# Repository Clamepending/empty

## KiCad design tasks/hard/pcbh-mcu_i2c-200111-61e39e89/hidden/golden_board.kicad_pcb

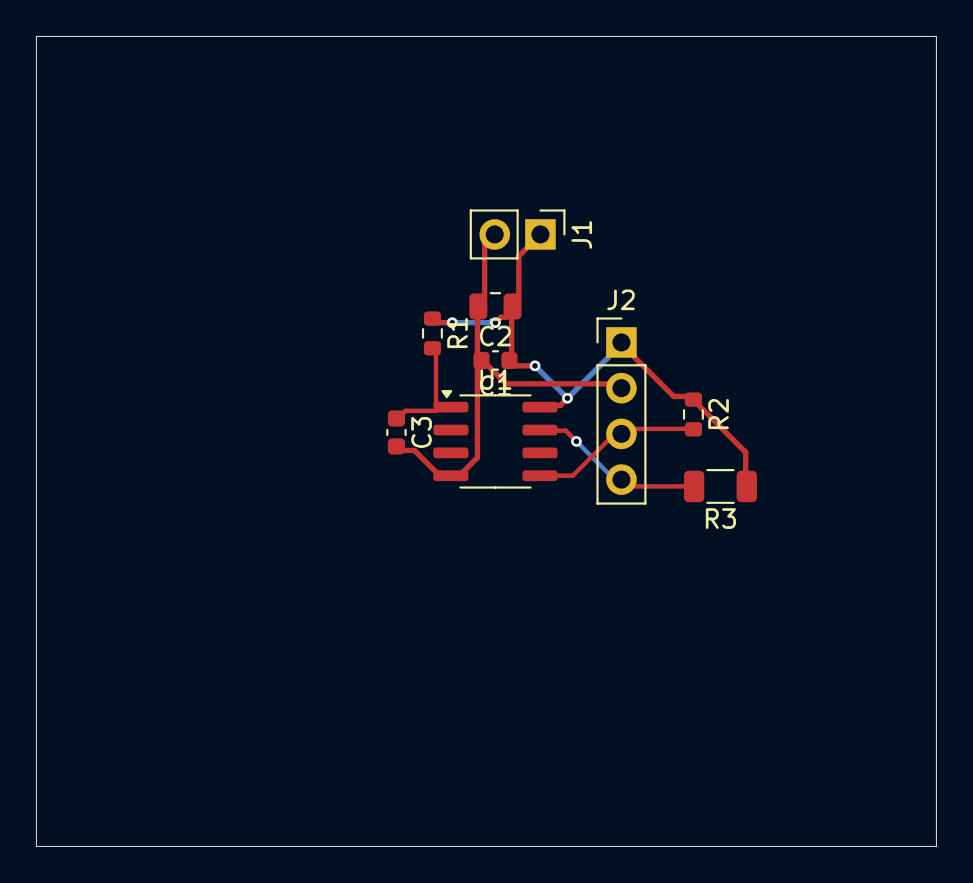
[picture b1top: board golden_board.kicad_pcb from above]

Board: 2 copper layers, 50.0 x 45.0 mm, 9 parts (0 on the bottom side), 5 nets.

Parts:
C1, C3: 100n; C_0603_1608Metric
C2: 1u; C_0805_2012Metric
J1: PinHeader_1x02_P2.54mm_Vertical
J2: PinHeader_1x04_P2.54mm_Vertical
R1: 7.5k; R_0603_1608Metric
R2: 16k; R_0603_1608Metric
R3: 16k; R_1206_3216Metric
U1: SOIC-8_3.9x4.9mm_P1.27mm

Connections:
+2V5: C1.1, C2.1, J1.1, J2.1, R1.1, R2.1, R3.1, U1.8
GND: C1.2, C2.2, C3.2, J1.2, J2.2, U1.4
NRST: C3.1, R1.2, U1.1
SCL: J2.4, R3.2, U1.7
SDA: J2.3, R2.2, U1.5

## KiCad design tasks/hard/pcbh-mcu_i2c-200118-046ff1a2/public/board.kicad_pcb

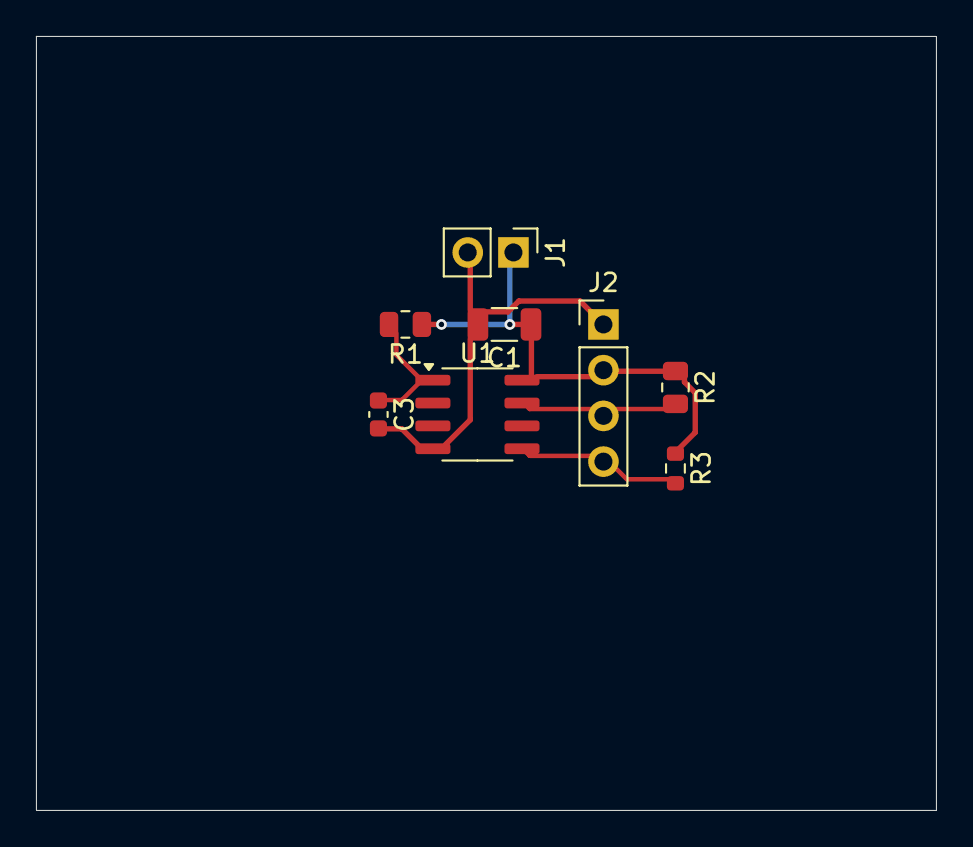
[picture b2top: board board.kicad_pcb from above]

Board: 2 copper layers, 50.0 x 43.0 mm, 8 parts (0 on the bottom side), 5 nets.

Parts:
C1: 100n; C_1206_3216Metric
C3: 100n; C_0603_1608Metric
J1: PinHeader_1x02_P2.54mm_Vertical
J2: PinHeader_1x04_P2.54mm_Vertical
R1: 5.1k; R_0805_2012Metric
R2: 8.2k; R_0805_2012Metric
R3: 390k; R_0603_1608Metric
U1: SOIC-8_3.9x4.9mm_P1.27mm

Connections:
+5V: C1.1, J1.1, J2.2, R1.1, R2.1, R3.1, U1.8
GND: C1.2, C3.2, J1.2, J2.1, U1.4
NRST: C3.1, R1.2, U1.1
SCL: J2.4, R3.2, U1.5
SDA: J2.3, R2.2, U1.7
